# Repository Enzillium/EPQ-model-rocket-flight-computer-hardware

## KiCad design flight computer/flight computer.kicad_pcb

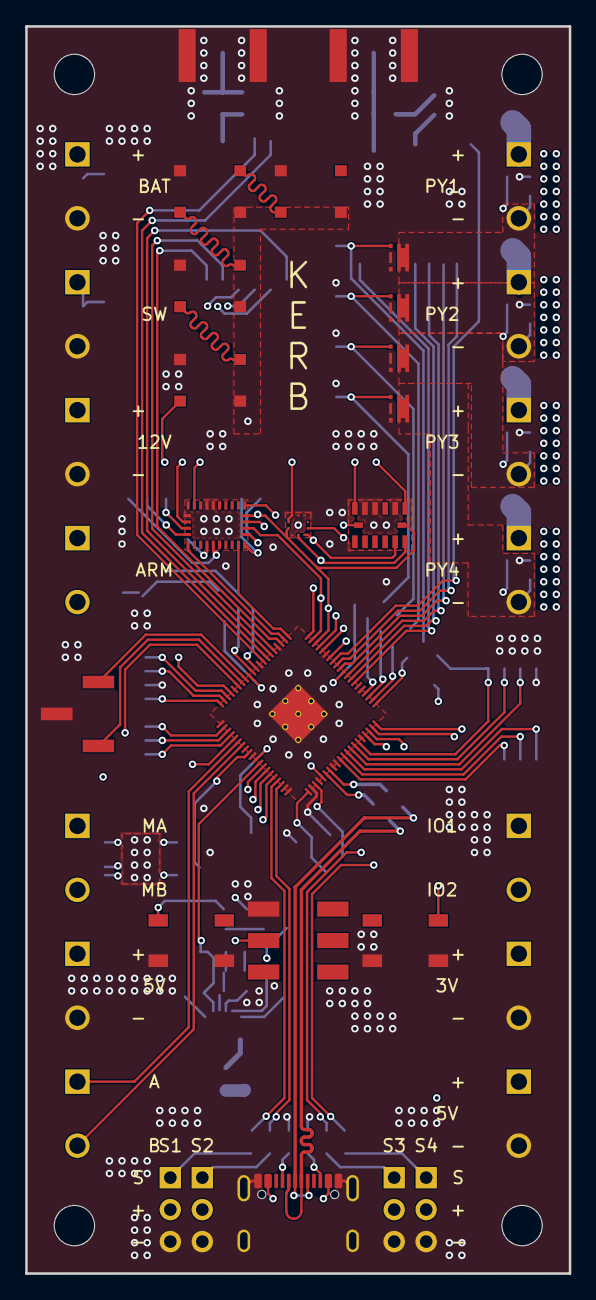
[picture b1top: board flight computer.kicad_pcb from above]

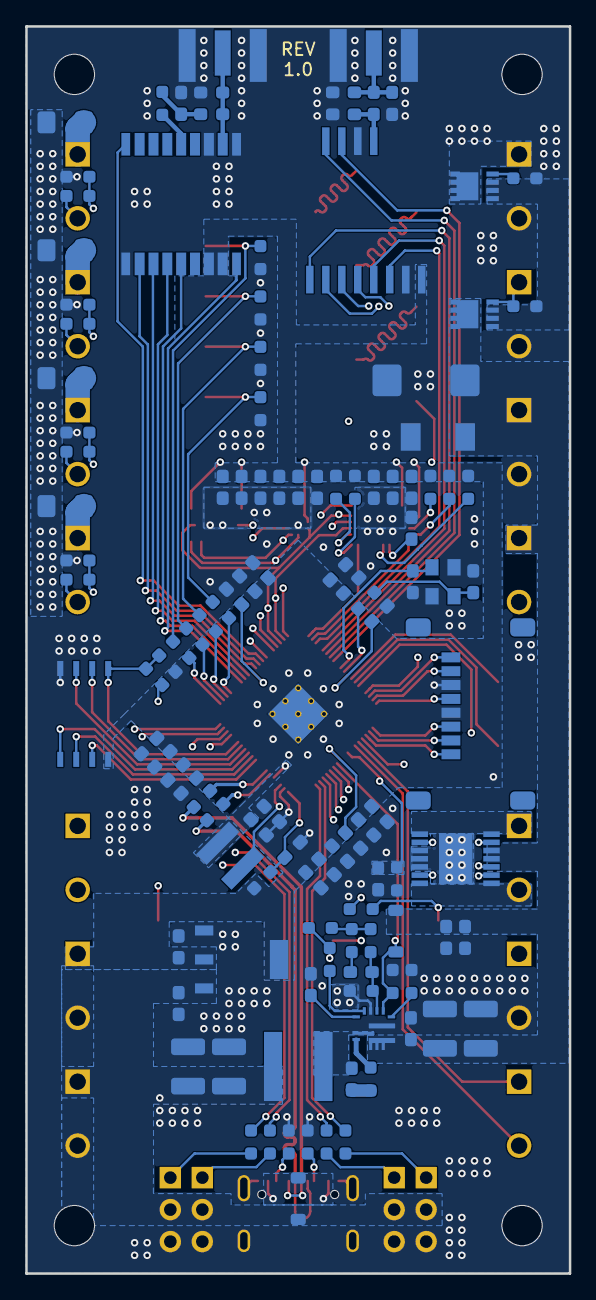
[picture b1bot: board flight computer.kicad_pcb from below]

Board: 4 copper layers, 43.2 x 99.1 mm, 158 parts (119 on the bottom side), 119 nets.

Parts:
C1, C2, C3, C4, C19, C36, C44, C49, C50: 4.7uF; C_0603_1608Metric_Pad1.08x0.95mm_HandSolder
C5, C6, C7, C8, C9, C10, C11, C12, C13, C14, C15, C18, C24, C28, C37, C38, C39, C42, C45, C46, C47, C48, C51, C53: 0.1uF; C_0603_1608Metric_Pad1.08x0.95mm_HandSolder
C16, C17: 15pF; C_0603_1608Metric_Pad1.08x0.95mm_HandSolder
C20, C21: 10uF; C_0603_1608Metric_Pad1.08x0.95mm_HandSolder
C22, C23: 10uF; C_1210_3225Metric_Pad1.33x2.70mm_HandSolder
C25: 47nF; C_0603_1608Metric_Pad1.08x0.95mm_HandSolder
C29: 150pF; C_0603_1608Metric_Pad1.08x0.95mm_HandSolder
C30, C31: 22uF; C_1210_3225Metric_Pad1.33x2.70mm_HandSolder
C40: 1nF; C_0603_1608Metric_Pad1.08x0.95mm_HandSolder
C41: 220uF; CAPMP7343X310N
C43: 10nF; C_0603_1608Metric_Pad1.08x0.95mm_HandSolder
C52, C54: 0; C_0603_1608Metric_Pad1.08x0.95mm_HandSolder
CR1: SMBJ15A; DO-214AASMB_J-BEND_LTF-L
D1, D2: D_TVS; D_0603_1608Metric_Pad1.05x0.95mm_HandSolder
D4: 8.7V; D_SOD-123
D5: D_Schottky; D_SOD-123
F1, F2, F3, F4: Fuse; Fuse_1206_3216Metric_Pad1.42x1.75mm_HandSolder
H1, H2, H3, H4: MountingHole; MountingHole_3.2mm_M3
IC1: AT25SF128A-SHB-T; IC8_AT25SF128A-SHB-T_ADO-L
IC2: 114993390
IC3: ADXL375BCCZ-RL; LGA_CC-14-1_ADI-L
J1: JST; PinHeader_1x03_P2.54mm_Vertical_SMD_Pin1Right
J2: battery in; 5452257
J3: battery sw; 5452257
J4: pyro sw; 5452257
J5: 12V out; 5452257
J6, J16: 5V out; 5452257
J7: 3.3V out; 5452257
J8: USB_C_Receptacle_USB2.0_16P; USB_C_Receptacle_GCT_USB4105-xx-A_16P_TopMnt_Horizontal
J9: GPIO; 5452257
J10: Micro_SD_Card; microSD_HC_Molex_47219-2001
J11: pyro 1; 5452257
J12: pyro 2; 5452257
J13: pyro 3; 5452257
J14: pyro 4; 5452257
J15: motor out; 5452257
J17: motor in; 5452257
J18: servo 1; PinHeader_1x03_P2.54mm_Vertical
J19: servo 2; PinHeader_1x03_P2.54mm_Vertical
J20: servo 3; PinHeader_1x03_P2.54mm_Vertical
J21: servo 4; PinHeader_1x03_P2.54mm_Vertical
J22, J23: SMA-J-P-H-ST-EM1; SAMTEC_SMA-J-P-H-ST-EM1
L1: 3.3uH; IND_TAIYO_NRS4018_TAY
L2: 3.3uH; L_Wurth_WE-XHMI-6030
L3: 27nH; L_0603_1608Metric_Pad1.05x0.95mm_HandSolder
L4: 0; L_0603_1608Metric_Pad1.05x0.95mm_HandSolder
LED1, LED2, LED3, LED4: COM-16347; COM-16347_SPK-L
Q4, Q5, Q6, Q7: SIA440DJ-T1-GE3; SIA440DJT1GE3
R3: 33; R_0603_1608Metric_Pad0.98x0.95mm_HandSolder
R4, R5: 27; R_0603_1608Metric_Pad0.98x0.95mm_HandSolder
R6, R7, R11, R35, R36, R37, R38, R46, R47, R48, R49: 1k; R_0603_1608Metric_Pad0.98x0.95mm_HandSolder
R8, R9, R16, R23, R27, R29, R31, R33, R50, R51, R52, R53: 100k; R_0603_1608Metric_Pad0.98x0.95mm_HandSolder
R10: 52.3k; R_0603_1608Metric_Pad0.98x0.95mm_HandSolder
R12, R15, R39, R40, R41, R43, R44: 10k; R_0603_1608Metric_Pad0.98x0.95mm_HandSolder
R13: 49.9; R_0603_1608Metric_Pad0.98x0.95mm_HandSolder
R14: 73.2k; R_0603_1608Metric_Pad0.98x0.95mm_HandSolder
R18, R19: 5.1k; R_0603_1608Metric_Pad0.98x0.95mm_HandSolder
R22: 820; R_0603_1608Metric_Pad0.98x0.95mm_HandSolder
R24, R25: 0; R_0603_1608Metric_Pad0.98x0.95mm_HandSolder
R28, R30, R32, R34: 27k; R_0603_1608Metric_Pad0.98x0.95mm_HandSolder
R42: 10; R_0603_1608Metric_Pad0.98x0.95mm_HandSolder
S1, S2: PTS647SM38SMTR2_LFS; PTS647SM38SMTR2LFS
S3: JS202011SCQN
U1: RP2350B; QFN-80-1EP_10x10mm_P0.4mm_EP3.4x3.4mm_ThermalVias
U4: AZ1117CH-3.3TRG1; SOT-223_DIO-L
U5: TPS56A37RPAR
U6, U11: SISS65DN-T1-GE3; POWERPAK-1212-8S_VIS
U7: BTM9011EP; SOP65P600X115-15N
U8: BMP581; QFN10_BMP581_BOS-L
U9: BNO086; IC_BNO086
U10: MAX-M10S-00B; XCVR_MAX-M10S-00B
Y1: ABM8-272-T3; XTAL_ABM8-272-T3

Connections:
+1.1V: C2.1, C3.1, C5.1, C6.1, L1.1, U1.10 (DVDD), U1.32 (DVDD), U1.51 (DVDD), U1.65 (VREG_FB)
+3.3V: C1.1, C7.1, C8.1, C9.1, C10.1, C11.1, C12.1, C13.1, C14.1, C15.1, C18.1, C19.1, C21.2, C36.1, C37.1, C42.1, C44.1, C45.1, C47.1, C48.1, C49.1, C50.1, C51.1, C53.1, IC1.8 (VCC), IC2.8 (VCC), IC3.1 (VDD_I/O), IC3.6 (VS), J7.1, J10.4 (VDD), J16.1, R3.2, R12.2, R39.1, R40.1, R41.1, R43.1, R44.2, U1.5 (IOVDD), U1.15 (IOVDD), U1.24 (IOVDD), U1.29 (IOVDD), U1.41 (IOVDD), U1.50 (IOVDD), U1.59 (ADC_AVDD), U1.60 (IOVDD), U1.64 (VREG_VIN), U1.68 (USB_OTP_VDD), U1.69 (QSPI_IOVDD), U1.76 (IOVDD), U4.2 (OUTPUT), U4.4 (EPAD), U8.1 (VDDIO), U8.10 (VDD), U9.3 (VDD), U9.28 (VDDIO), U10.7 (V_IO), U10.8 (VCC)
+5V: C20.2, C30.2, C31.2, D5.1 (K), J6.1, J18.2, J19.2, J20.2, J21.2, L2.2, LED1.1 (VDD), LED2.1 (VDD), LED3.1 (VDD), LED4.1 (VDD), R13.2, R23.2, U4.3 (INPUT)
+12V: C22.2, C23.2, C24.2, C38.1, C39.1, C41.1, CR1.1, D4.1 (K), J4.1, J5.1, U5.8 (VIN), U5.11 (VIN), U5.12 (VIN), U5.13 (VIN), U6.5 (D), U6.6 (D), U6.7 (D), U6.8 (D), U7.11 (VS@2), U7.12 (VS@1)
+12V pyro: F1.1, F2.1, F3.1, F4.1, J4.2
+VBAT: J2.1, U11.5 (D), U11.6 (D), U11.7 (D), U11.8 (D)
+VBAT safe: R8.1, U6.1 (S), U6.2 (S), U6.3 (S), U11.1 (S), U11.2 (S), U11.3 (S)
/ADXL375 CS: IC3.7 (~CS), U1.14 (GPIO15)
/BMP581 CS: U1.16 (GPIO16), U8.6 (CSB)
/BNO086 CS: U1.17 (GPIO17), U9.18 (~H_CS)
/BNO086 int: U1.21 (GPIO21), U9.14 (~H_INT)
/BNO086 wake: U1.22 (GPIO22), U9.6 (PS0/WAKE)
/BTM9011EP CS: U1.45 (GPIO36), U7.10 (CS)
/BTM9011EP IS: C40.1, R22.2, U1.49 (GPIO40/ADC0), U7.13 (IS)
/LED controller: LED1.4 (DIN), U1.37 (GPIO29)
/MAX M10S RX: U1.11 (GPIO12), U10.3 (RXD)
/MAX M10S TX: U1.12 (GPIO13), U10.2 (TXD)
/MAX M10S boot: U1.13 (GPIO14), U10.18 (~SAFEBOOT)
/MAX M10S int: U1.8 (GPIO10), U10.5 (EXTINT)
/MAX M10S reset: U1.7 (GPIO9), U10.9 (~RESET)
/MAX M10S timepulse: U1.9 (GPIO11), U10.4 (TIMEPULSE)
/MCU_DN: R4.1, U1.66 (USB_DN)
/MCU_DP: R5.1, U1.67 (USB_DP)
/MISO: IC2.2 (MISO), IC3.12 (SDO/ALT_ADDRESS), U1.20 (GPIO20), U7.9 (SDO), U8.5 (SDO), U9.20 (H_SDA/H_MISO/TX)
/MOSI: IC2.3 (MOSI), IC3.13 (SDA/SDI/SDIO), U1.19 (GPIO19), U7.2 (SDI), U8.4 (SDI), U9.17 (SA0/H_MOSI)
/QSPI_SCLK: IC1.6 (SCK), U1.71 (QSPI_SCLK)
/QSPI_SD0: IC1.5 (SI_(I/O0)), U1.72 (QSPI_SD0)
/QSPI_SD1: IC1.2 (SO_(I/O1)), U1.74 (QSPI_SD1)
/QSPI_SD2: IC1.3 (~WP_(I/O2)), U1.73 (QSPI_SD2)
/QSPI_SD3: IC1.7 (~HOLD_(I/O3)), U1.70 (QSPI_SD3)
/QSPI_SS: IC1.1 (~CS), R7.1, R12.1, U1.75 (~QSPI_SS)
/SCK: IC2.4 (SCK), IC3.14 (SCL/SCLK), U1.18 (GPIO18), U7.6 (SCLK), U8.2 (SCK), U9.19 (H_SCL/SCK/RX)
/SD CLK: J10.5 (CLK), U1.40 (GPIO32)
/SD CMD: J10.3 (CMD), U1.42 (GPIO33)
/SD DAT0: J10.7 (DAT0), U1.39 (GPIO31)
/SD DAT1: J10.8 (DAT1), U1.38 (GPIO30)
/SD DAT2: J10.1 (DAT2), U1.44 (GPIO35)
/SD DAT3: J10.2 (DAT3/CD), U1.43 (GPIO34)
/SWCLK: J1.1, U1.33 (SWCLK)
/SWDIO: J1.3, U1.34 (SWDIO)
/SX1262 CS: IC2.6 (NSS), U1.23 (GPIO23)
/SX1262 busy: IC2.11 (BUSY), U1.28 (GPIO27)
/SX1262 int: IC2.12 (DIO1), U1.27 (GPIO26)
/SX1262 reset: IC2.5 (NRST), U1.25 (GPIO24)
/SX1262 rf switch: IC2.1 (RF_SW_), U1.26 (GPIO25)
/USB_DN: J8.A7 (D-), J8.B7 (D-), R4.2
/USB_DP: J8.A6 (D+), J8.B6 (D+), R5.2
/XIN: C16.2, U1.30 (XIN), Y1.1
/XOUT: R6.1, U1.31 (XOUT)
/gate: J3.1, R8.2, S3.2, U6.4 (G)
/motor in a: J17.1, U1.46 (GPIO37)
/motor in b: J17.2, U1.47 (GPIO38)
/motor out a: J15.1, U7.1 (OUTA1), U7.14 (OUTA2)
/motor out b: J15.2, U7.7 (OUTB1), U7.8 (OUTB2)
/pin out 1: J9.1, U1.80 (GPIO3)
/pin out 2: J9.2, U1.79 (GPIO2)
/power signal: D4.2 (A), R16.1, U1.52 (GPIO41/ADC1), U5.1 (EN)
/pyro 1 continuity: R27.2, R28.1, U1.53 (GPIO42/ADC2)
/pyro 1 drain: J11.2, Q7.1 (D_1), Q7.2 (D_2), Q7.5 (D_3), Q7.6 (D_4), Q7.D1 (D_5), R27.1
/pyro 1 gate: R49.1, U1.1 (GPIO4)
/pyro 2 continuity: R29.2, R30.1, U1.54 (GPIO43/ADC3)
/pyro 2 drain: J12.2, Q4.1 (D_1), Q4.2 (D_2), Q4.5 (D_3), Q4.6 (D_4), Q4.D1 (D_5), R29.1
/pyro 2 gate: R46.1, U1.2 (GPIO5)
/pyro 3 continuity: R31.2, R32.1, U1.55 (GPIO44/ADC4)
/pyro 3 drain: J13.2, Q5.1 (D_1), Q5.2 (D_2), Q5.5 (D_3), Q5.6 (D_4), Q5.D1 (D_5), R31.1
/pyro 3 gate: R47.1, U1.3 (GPIO6)
/pyro 4 continuity: R33.2, R34.1, U1.56 (GPIO45/ADC5)
/pyro 4 drain: J14.2, Q6.1 (D_1), Q6.2 (D_2), Q6.5 (D_3), Q6.6 (D_4), Q6.D1 (D_5), R33.1
/pyro 4 gate: R48.1, U1.4 (GPIO7)
/servo PWM 1: R35.1, U1.57 (GPIO46/ADC6)
/servo PWM 2: R36.1, U1.58 (GPIO47/ADC7)
/servo PWM 3: R37.1, U1.77 (GPIO0)
/servo PWM 4: R38.1, U1.78 (GPIO1)
GND: C1.2, C2.2, C3.2, C4.2, C5.2, C6.2, C7.2, C8.2, C9.2, C10.2, C11.2, C12.2, C13.2, C14.2, C15.2, C16.1, C17.1, C18.2, C19.2, C20.1, C21.1, C22.1, C23.1, C24.1, C25.1, C30.1, C31.1, C36.2, C37.2, C38.2, C39.2, C40.2, C41.2, C42.2, C43.2, C44.2, C45.2, C46.2, C47.2, C48.2, C49.2, C50.2, C51.2, C52.2, C53.2, C54.2, CR1.2, D1.1 (A1), D2.1 (A1), IC1.4 (GND), IC2.7 (GND_1), IC2.10 (GND_2), IC3.2 (GND_1), IC3.4 (GND_2), IC3.5 (GND_3), J1.2, J2.2, J3.2, J5.2, J6.2, J7.2, J8.A1 (GND), J8.A12 (GND), J8.B1 (GND), J8.B12 (GND), J8.SH (SHIELD), J10.6 (VSS), J16.2, J18.3, J19.3, J20.3, J21.3, J22.2_1, J22.2_2, J22.3_1, J22.3_2, J23.2_1, J23.2_2, J23.3_1, J23.3_2, LED1.3 (VSS), LED2.3 (VSS), LED3.3 (VSS), LED4.3 (VSS), Q4.4 (S_1), Q4.D2 (S_2), Q5.4 (S_1), Q5.D2 (S_2), Q6.4 (S_1), Q6.D2 (S_2), Q7.4 (S_1), Q7.D2 (S_2), R9.2, R10.1, R15.1, R16.2, R18.2, R19.2, R22.1, R28.2, R30.2, R32.2, R34.2, R50.2, R51.2, R52.2, R53.2, S1.3 (COM_1), S1.4 (COM_2), S2.3 (COM_1), S2.4 (COM_2), S3.1, U1.62 (VREG_PGND), U1.81 (GND), U4.1 (ADJ/GND), U5.3 (AGND), U5.9 (PGND), U7.3 (GND@3), U7.4 (GND@2), U7.5 (GND@1), U7.15 (EDP), U8.3 (VSS), U8.8 (VSS), U8.9 (VSS), U9.2 (GND), U9.25 (GNDIO), U9.26 (XOUT32/CLKSEL1), U10.1 (GND), U10.10 (GND__1), U10.12 (GND__2), Y1.2, Y1.4
unnamed: C17.2, R6.2, Y1.3
unnamed: C28.2, R25.1
unnamed: C29.2, R24.2
unnamed: C43.1, L3.2, R42.1
unnamed: C54.1, D1.2 (A2), J23.1, L4.2
unnamed: D2.2 (A2), J22.1, L3.1, U10.11 (RF_IN)
unnamed: D5.2 (A), J8.A4 (VBUS), J8.A9 (VBUS), J8.B4 (VBUS), J8.B9 (VBUS)
unnamed: F1.2, J11.1
unnamed: F2.2, J12.1
unnamed: F3.2, J13.1
unnamed: F4.2, J14.1
unnamed: C52.1, IC2.9 (ANT), L4.1
unnamed: J8.A5 (CC1), R18.1
unnamed: J8.B5 (CC2), R19.1
unnamed: J18.1, R35.2
unnamed: J19.1, R36.2
unnamed: J20.1, R37.2
unnamed: J21.1, R38.2
unnamed: LED1.2 (DOUT), LED2.4 (DIN)
unnamed: LED2.2 (DOUT), LED3.4 (DIN)
unnamed: LED3.2 (DOUT), LED4.4 (DIN)
unnamed: Q4.3 (G), R46.2, R50.1
unnamed: Q5.3 (G), R47.2, R51.1
unnamed: Q6.3 (G), R48.2, R52.1
unnamed: Q7.3 (G), R49.2, R53.1
unnamed: R13.1, R14.2, R24.1
unnamed: R7.2, S1.2 (NO_2)
unnamed: R11.1, S2.1 (NO_1)
unnamed: R11.2, U1.35 (RUN)
unnamed: C4.1, R3.1, U1.61 (VREG_AVDD)
unnamed: L1.2, U1.63 (VREG_LX)
unnamed: R25.2, U5.7 (BOOT)
unnamed: C29.1, R14.1, R15.2, U5.2 (FB)
unnamed: R10.2, U5.10 (MODE)
unnamed: R23.1, U5.4 (PG)
unnamed: C25.2, U5.5 (SS)
unnamed: C28.1, L2.1, U5.6 (SW)
unnamed: C46.1, U9.9 (CAP)
unnamed: R41.2, U9.10 (CLKSEL0)
unnamed: R43.2, U9.15 (ENV_SCL)
unnamed: R44.1, U9.16 (ENV_SDA)
unnamed: R40.2, U9.5 (PS1)
unnamed: R39.2, U9.4 (~BOOT)
unnamed: R42.2, U10.14 (VCC_RF)
unnamed: R9.1, U11.4 (G)

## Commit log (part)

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2026-05-19 5V buck regulator added
2026-05-21 BMP581 barometer added
2026-05-21 BNO086 IMU added
2026-05-21 BTM9011EP motor controller added
2026-05-22 MAX M10S GNSS added
2026-06-07 SX1262 added
2026-06-07 AZ1117CH 3.3V LDO added
2026-06-09 On/Off circuit added
2026-06-09 ADXL375 accelerometer added
2026-06-10 VND9025 high-side switch added
2026-06-10 Buzzer added
2026-06-10 Reverse polarity protection added
2026-06-12 TVS diode added
2026-06-12 SD card added
2026-06-14 USB C added
2026-06-14 Pyro MOSFETs added
2026-06-14 LEDs added
2026-06-14 Switch added
2026-06-14 Organising the schematic
2026-06-21 Finalisation of Schematic
